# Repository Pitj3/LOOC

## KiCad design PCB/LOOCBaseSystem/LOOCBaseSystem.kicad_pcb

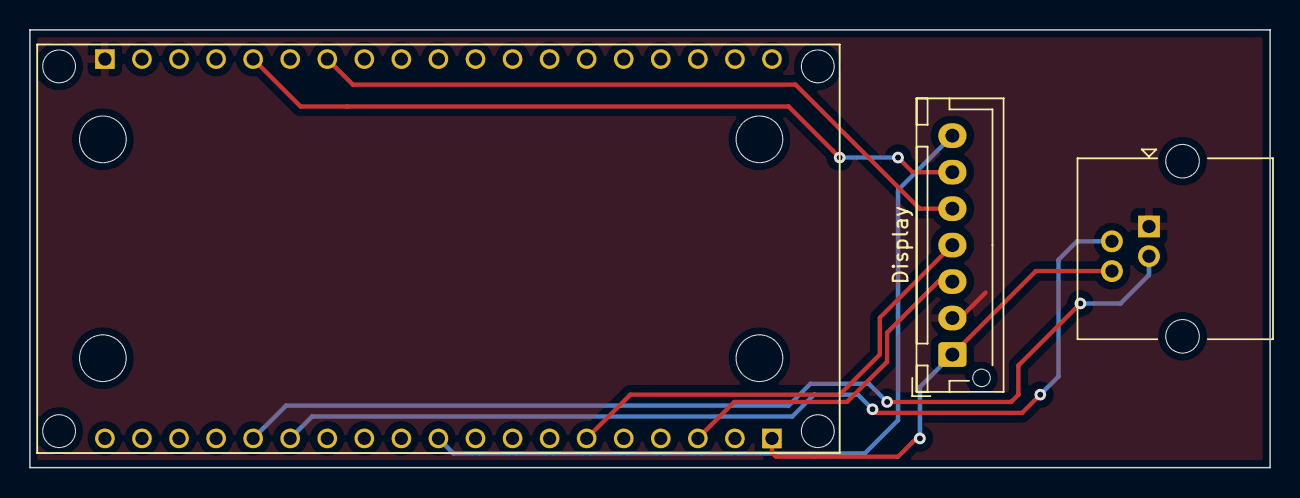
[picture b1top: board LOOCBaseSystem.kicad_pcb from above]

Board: 2 copper layers, 85.0 x 30.0 mm, 7 parts (0 on the bottom side), 9 nets.

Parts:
Display: ScreenConnector; JST_XH_B7B-XH-AM_1x07_P2.50mm_Vertical
H1, H2, H3, H4: MountingHole; MountingHole_3.2mm_M3
J1: RJ14; RJ14_Connfly_DS1133-S4_Horizontal
U1: ESP32_NODEMCU; MODULE_ESP32_NODEMCU

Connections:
CS: Display.7, U1.J4_10 (G5)
DATA_A: J1.2, U1.J4_14 (G0)
DATA_B: J1.3, U1.J4_15 (G2)
DC: Display.6, U1.J5_5 (G13)
GND: Display.1, J1.4, U1.J4_1 (GND), U1.J4_7 (GND), U1.J5_6 (GND)
RST: Display.5, U1.J5_7 (G12)
SCL: Display.3, U1.J4_3 (G22)
SDA: Display.4, U1.J4_6 (G21)
VCC: Display.2, J1.1, U1.J5_1 (5V)

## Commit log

2022-12-05 KiCAD PCB Project and Step files for Base Controller construction
